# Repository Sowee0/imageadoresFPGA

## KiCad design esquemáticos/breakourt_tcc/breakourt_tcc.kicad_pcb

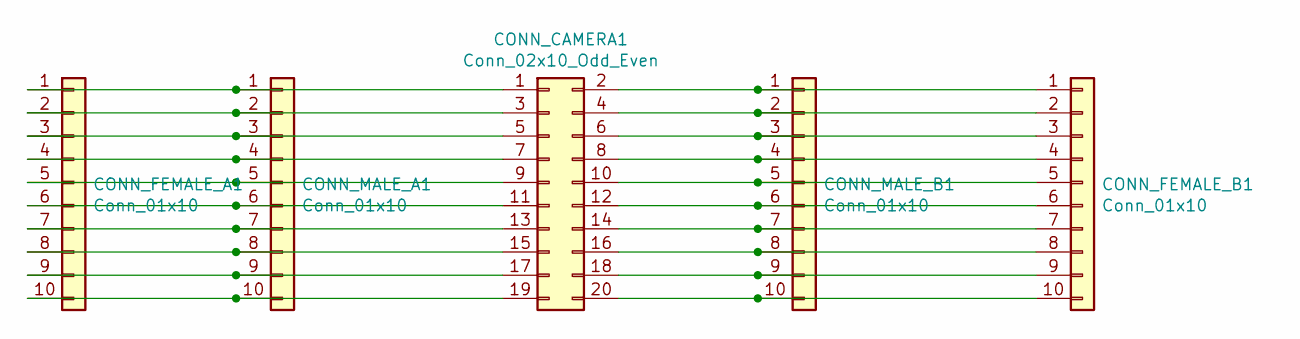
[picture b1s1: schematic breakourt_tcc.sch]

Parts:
CONN_CAMERA1: Conn_02x10_Odd_Even; PinHeader_2x10_P2.54mm_Vertical
CONN_FEMALE_A1: Conn_01x10; PinHeader_1x10_P2.54mm_Vertical
CONN_FEMALE_B1: Conn_01x10; PinHeader_1x10_P2.54mm_Vertical
CONN_MALE_A1: Conn_01x10; PinHeader_1x10_P2.54mm_Vertical
CONN_MALE_B1: Conn_01x10; PinHeader_1x10_P2.54mm_Vertical

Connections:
unnamed: CONN_CAMERA1.1, CONN_FEMALE_A1.1, CONN_MALE_A1.1
unnamed: CONN_CAMERA1.2, CONN_FEMALE_B1.1, CONN_MALE_B1.1
unnamed: CONN_CAMERA1.3, CONN_FEMALE_A1.2, CONN_MALE_A1.2
unnamed: CONN_CAMERA1.4, CONN_FEMALE_B1.2, CONN_MALE_B1.2
unnamed: CONN_CAMERA1.5, CONN_FEMALE_A1.3, CONN_MALE_A1.3
unnamed: CONN_CAMERA1.6, CONN_FEMALE_B1.3, CONN_MALE_B1.3
unnamed: CONN_CAMERA1.7, CONN_FEMALE_A1.4, CONN_MALE_A1.4
unnamed: CONN_CAMERA1.8, CONN_FEMALE_B1.4, CONN_MALE_B1.4
unnamed: CONN_CAMERA1.9, CONN_FEMALE_A1.5, CONN_MALE_A1.5
unnamed: CONN_CAMERA1.10, CONN_FEMALE_B1.5, CONN_MALE_B1.5
unnamed: CONN_CAMERA1.11, CONN_FEMALE_A1.6, CONN_MALE_A1.6
unnamed: CONN_CAMERA1.12, CONN_FEMALE_B1.6, CONN_MALE_B1.6
unnamed: CONN_CAMERA1.13, CONN_FEMALE_A1.7, CONN_MALE_A1.7
unnamed: CONN_CAMERA1.14, CONN_FEMALE_B1.7, CONN_MALE_B1.7
unnamed: CONN_CAMERA1.15, CONN_FEMALE_A1.8, CONN_MALE_A1.8
unnamed: CONN_CAMERA1.16, CONN_FEMALE_B1.8, CONN_MALE_B1.8
unnamed: CONN_CAMERA1.17, CONN_FEMALE_A1.9, CONN_MALE_A1.9
unnamed: CONN_CAMERA1.18, CONN_FEMALE_B1.9, CONN_MALE_B1.9
unnamed: CONN_CAMERA1.19, CONN_FEMALE_A1.10, CONN_MALE_A1.10
unnamed: CONN_CAMERA1.20, CONN_FEMALE_B1.10, CONN_MALE_B1.10

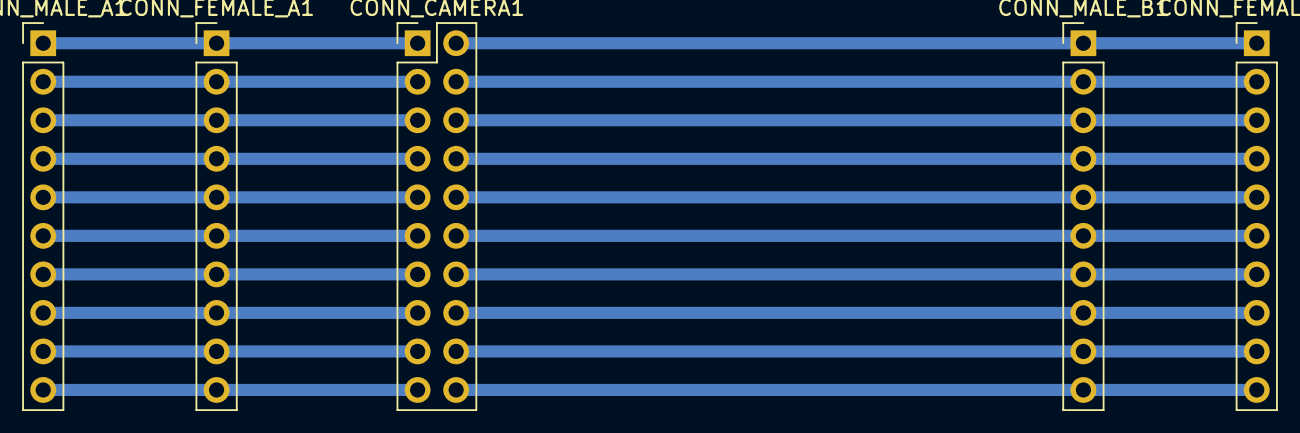
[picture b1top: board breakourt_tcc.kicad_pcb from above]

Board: 2 copper layers, 5 parts (0 on the bottom side), 20 nets.

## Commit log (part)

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2019-06-03 Adicionando os primeiros arquivos de teste
2019-06-03 Reorganizando o projeto
2019-06-03 mexendo no teste de mudança
2019-06-07 Adicionando o código para mudar página e imprimir o endereço selecionado
2019-06-07 Adicionando o esboço do protótipo de aquisição de imagem
2019-06-07 Adicionando as definições dos pinos e setando-os como output
2019-06-08 Adicionando uma exibição binária dos valores lidos
2019-06-08 Adicionando a inversão de bytes na escrita de registradores e corrigindo alguns erros de cout
2019-06-08 Adicionando um ignore para os arquivos executáveis gerados
2019-06-08 Adicionando o esboço de um script para compilar todos os arquivos e salvá-los em ./build/
2019-06-08 Adicionando um ignore pros arquivos do VScode
2019-06-08 Reorganizando o main(), adicionando funções de setup e loop
2019-06-09 Mudando a ordem do cabeçalho
2019-06-09 Corrigindo a ordem e adicionando comentários ao Setup()
2019-06-09 Adicionando o esboço do código que muda de YUV pra RGB
2019-06-09 Atualizando o gitignore para remover outras pastas do vscode
2019-06-09 Definindo alguns parâmetros da posição de memória
2019-06-09 Reorganizando e renomeando variáveis
2019-06-09 Adicionando comentários relevantes
2019-06-09 Adicionando a mudança para RGB e checagem da mesma
2019-06-09 Correções finais simples de posição
2019-06-09 Corrigindo a inicialização da camera para um endereço definido a priori
2019-06-09 Adicionando um script simples para iniciar o clock da câmera
2019-06-09 Corrigindo um erro no script
2019-06-09 Mudando as permissões do script de início e arrumando a variável no código que não poderia ser constante
2019-06-09 Mudando a verificação de página
2019-06-10 Corrigindo o registrador inicial da página 1
2019-06-10 Adicionando uma verificação do valor a ser escrito
2019-06-10 Corrigindo um assignment no lugar de comparação
2019-06-10 Testando o VScode
2019-06-10 Adicionando a função de início do wiringPi aos dois arquivos
2019-06-10 Trocando as definições por constantes
2019-06-10 Mudando o modo de inicio dos pinos a serem usados com interrupção
2019-06-10 Esboçando as funções de interrupção e adicionando uma conversao de portas para byte
2019-06-10 Adicionando o inicializador obrigatório pro wiringPi
2019-06-10 Movendo variaveis de lugar e removendo código antigo
2019-06-10 Adicionando o esquemático do breakout da câmera
2019-08-17 Adicionando uma cópia para testes rápidos
2019-08-19 adding another simples test
2019-08-19 mudando a ordem dos pinos
2019-08-19 consertando o nome do arquivo
2019-08-19 corrigindo erros na implementação do ISR
2019-08-19 corrigindo a confusao de arquivos
2019-08-19 adicionando a biblioteca faltante do wiringpi
2019-08-19 testando um approach que não trave o raspberry
2019-08-20 adicionando uma saida para que o programa não trave o raspberry
2019-08-20 corrigindo o parametro do exit
2019-08-23 teste
2019-08-23 construindo o novo imagetest melhorado
2019-08-23 Corrigindo a abertura de arquivo
2019-08-23 corrigindo a virgula faltante do CSV
2019-08-24 adicionando a função de leitura
2019-08-24 consertando a posição da chamdada
2019-08-25 adicionando um controle de interrupção
2019-08-25 corrigindo a desativaçãod e interrupção
2019-08-25 corrigindo um typo no script
2019-08-25 corrigindo a primeira linha dos scripts
2019-08-25 mudando as permissões do script no linux
2019-08-25 corrigindo um comparados do script
2019-08-25 adicionando a prioridade de modo a diminuir o lockup do raspberry por causa das interrupcoes
2019-09-09 Adicionando os arquivos relacionados ao projeto em verilog
2019-09-13 Corrigindo o gitignore para ignorar todos os arquivos gerados pelo projeto
2019-09-13 adicionando todos os arquivos do projeto
2019-09-18 Atualizando o gitignore para excluir os outputs do quartus
2019-09-18 Implementação da FLASH e adicionando arquivos de projeto do quartus
2019-09-20 Adicionando um monte de testes
2019-10-08 Adicionando testes em matlab para a pesquisa de pupila
2019-10-08 Adicionando um pequeno teste com o teensy para controlar a camera via i2c
2019-10-08 Adicionando mudanças no código em verilog
2019-10-10 Adicionando outros arquivos para pesquisa e mexendo no código
2019-10-11 Mudanca nas variaveis e adicao de maisv testes
2019-10-23 Mudar o gitignore
2019-10-23 Adicionando mudanças no código em matlab
2019-10-23 adicionando o código base e o meu juntos
2019-10-23 Removendo os testes e voltando o arquivo para seu ponto inicial
2019-10-23 Atualizando com o codigo que estava antes no vga_controller
2019-10-23 Atualizando os parâmetros passados para o modulo
2019-10-23 Corrigindo o caminho pois o projeto mudou de lugar
2019-10-23 Adicionando uma verificação vertical simples
2019-10-23 mudando o nome do módulo
2019-10-23 Fazendo algumas mudanças no acesso da SDRAM
2019-10-24 Fixando a saída pro teste de pesquisa de pupila
2019-10-24 Mudando algumas definições de saida para tempo zero
2019-10-24 Adicionando a entrada de memoria no TESTMODULE
2019-10-24 Consertando a contagem de frames que não entrava no SRAM_TST
2019-10-24 Adicionando o código que escreve na SRAM e depois lê a posição
2019-10-24 Tirando a posição fixa e recebendo-a de outro módulo
2019-10-25 Adicionando o modulo de acesso de memoria por coordenadas
2019-10-30 Adicionando os novos arquivos e colocando-os no projeto
2019-10-30 Mudando a pasta da pesquisa de pupila em matlab de lugar
2019-10-30 Criação de um código em matlab que lê uma imagem e transforma em memoria em verilog
2019-10-31 Mudando o nome de algumas variáveis e corrigindo seus tamanhos
2019-10-31 Adicionando uma logica de avaliação de correlação
2019-10-31 Corrigindo o tamanho das variáveis
2019-10-31 Adicionando as variáveis de controle
2019-10-31 Adicionando uma imagem gerada previamente pelo código de matlab
2019-10-31 Adicionando os novos arquivos ao projeto
2019-10-31 Adicionando o controlador que seleciona o melhor ponto (maior correlação)
2019-11-07 corrigindo tabulação
2019-11-07 Corrigindo a sintaxe de verilog que estava sendo gerada errada
2019-11-07 Adicionando parametros para ajudar na aquisição do frame diminuído
2019-11-09 Corrigindo vírgulas desnecessárias
2019-11-09 Corrigindo mais uma virgula desnecessaria
2019-11-09 Adicionando o controller.v ao projeto
2019-11-09 Corrigindo a sintaxe errada
2019-11-09 Truncando o range do verde
2019-11-09 Corrigindo a falta de uma variável com memoria
2019-11-09 Corrigindo o nome da variável e mudando a lista de sensitividade
2019-11-09 Corrigindo a lista de sensibilidade e o tipo de variável
2019-11-11 Adicionando o novo teste procuraPupila2
2019-11-11 Erro de gramática
2019-11-11 Removendo a associação de leds a switches e adicionando o SAVE_FRAME
2019-11-11 Escrevendo o SAVE_FRAME e adicionando-o ao projeto
2019-11-11 Atualizando o readme
2019-11-12 Adicionando uma versão compilavel do software da de2-115
2019-11-12 mexendo no save_frame tanto em si quanto na inicialização
2019-11-13 Removendo arquivos desnecessários do projeto base
2019-11-13 Configurando a saída para 640x480x60
2019-11-13 Implementando a conversão pra escala de cinza
2019-11-13 Adicionando uma saída da posição do VGA
2019-11-13 Adicionando o SAVE_FRAME e configurando-o no projeto
2019-11-14 Adicionando os arquivos do projeto anterior
2019-11-14 Mudando o nome para SRAM_INTERFACE
2019-11-14 Corrigindo o nome da variável de endereço de memória
2019-11-15 Implementando algumas entradas da memoria
2019-11-16 Adicionando a implementação de todos os módulos
2019-11-16 Adicionando uma descrição às portas
2019-11-16 Adicionando uma descrição as portas
2019-11-16 corrigindo o tamanho da pesquisa
2019-11-16 Mudando o valor de offset pro disponível no arquivo de parametros
2019-11-16 removendo comentários
2019-11-16 Adicionando mais uma porta de endereço para dividir saida e entrada
2019-11-16 Adicionando uma significação de maneira a escolher de onde buscar o endereço
2019-11-16 removendo variáveis não usadas
2019-11-16 Mudando para non-blocking
2019-11-16 adicionando um tamanho aos valores
2019-11-16 Mudando algumas posições e adicionando valores
2019-11-18 Mudando a implementação para remover os multiplos always
2019-11-19 Adicionando a placa do anel de LED
2019-11-19 Adicionando clocks aos modulos que não o tinham
2019-11-19 Adicionando tamanhos para as definições
2019-11-19 Corrigindo a falta de tamanho dos vetores
2019-11-19 Adicionando o fio para interromper a captura
2019-11-19 Adicionando um led de status para a correlação
2019-11-19 Removendo uma conexão não usada
2019-11-19 Removendo conexões e registradores não usados
2019-11-19 Adicionando tamanhos faltantes nos vetores de dados
2019-11-19 Adicionando o led de status da correlação
2019-11-19 Adicionando tamanho para os números
2019-11-19 Adicionando um contador para fazer o led de status piscar
2019-11-19 Adicionando várias inicializações para registradores
2019-11-19 Corrigindo o projeto
2019-11-20 Atualizando a simplificação da pupila
2019-11-20 Corrigindo o codigo com a imagem certa e adicionando-a
2019-11-20 Corrigindo a condição do if
2019-11-20 Corrigindo o tamanho dos registradores
2019-11-20 Mudando os displays
2019-11-20 Adicionando um testbench para testar o coord2addr
2019-11-20 Adicionando uma inicialização faltante
2019-11-20 Adicionando um testbench ao IMG_SEARCH
2019-11-20 Corrigindo a falta de inicialização
2019-11-20 Adicionando um ignore pra arquivos cdf
2019-11-20 Adicionando ao projeto configurações de simulação
2019-11-21 ativando o signaltap
2019-11-21 tentando corrigir a transformação
2019-11-21 Mudando inicializações e tentando reordenar o fim
2019-11-21 Testando instancias do signaltap
2019-11-21 Adicionando um testbench para o controller
2019-11-21 Adicionando uma saída para quando pronto
2019-11-21 Problema da contagem resolvido!
2019-11-21 Corrigindo a pesquisa de pixel
2019-11-21 Trazendo a condição de volta
2019-11-21 testando um novo signaltap
2019-11-21 definições de projeto atualizadas
2019-11-21 Corrigindo a logica
2019-11-21 Criando um testbench para o current_score
2019-11-21 Atualizando arquivos do projeto
2019-11-22 Corrigindo o falta de conexão dos dados da SRAM e pesquisa
2019-11-22 Removendo o check no finish e mudando a resolução de pesquisa
2019-11-22 Mudando a implementação do grayscale e adicionando um controle de XY
2019-11-22 Adicionando fios para acomodar a nova implementação do grayscale
    adicionando também ligações com os módulos necessários
2019-11-22 adicionando a merda dos arquivos do projeto
2019-11-22 Movendo as coisas para um always regido pelo finished
2019-11-22 Voltando com a implementação antiga
2019-11-22 Diminuindo os parâmetros para uma simulação mais rápida
2019-11-22 Diminuindo parametros de teste
2019-11-22 Mudando parâmetros e mudando o comparador de lugar
2019-11-22 Escrevendo um testbench que relaciona ambos os módulos
2019-11-22 Editando parametros
2019-11-22 Editando arquivos do projeto e adicionando um signaltap
2019-11-22 Versão finalizada do conversor em matlab
2019-11-22 Adicionando um fio de controle ao controller e corr_score
2019-11-23 voltando para a resolução original
2019-11-23 Adicionando uma marcação para o ponto de pesquisa
2019-11-23 Adicionando uma verificação para pontos fora da imagem
2019-11-23 Atualizando com o ultimo codigo gerado pelo matlab
2019-11-23 Atualizando o signaltap e arquivos do projeto
2019-11-23 Corrigindo um número escrito na base errada
2019-11-24 Corrigindo uma ligação de tamanho errado
2019-11-24 Corrigindo a ordem de pixels da imagem salva na SRAM
2019-11-24 Mudando a contagem de frames para algo mais cedo
2019-11-26 Mudando a ordem do save_frame para parar a captura
2019-11-26 Adicionando uma saída da exposição
2019-11-26 Conectando a exposição mostrada aos displays de 7 segmentos
2019-11-29 Testando uma nova implementação
2020-03-20 Adicionando arquivos de olho e mudando o codigo
2020-04-03 Modificando os parametros para ter uma imagem menor e pesquisa também
2020-04-03 Adicionando uma definição de metade de frame e colocando-a nos parametros
2020-04-03 Modificando o bit shift para que divida por 3 e não 4 devido a mudança de resolução
